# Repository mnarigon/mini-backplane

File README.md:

## A 4-slot S-100 bus mini-backplane with power supply chassis.

#### Description

This is a 4-slot S-100 bus mini-backplane with power supply chassis.

It is intended for someone interested in building and running S-100 bus cards, possibly as a first project or for use on a test bench.

Features:
- 4 slots.
- Chassis is designed for three Mean Well switching power supplies to provide 8V, 16V, and -16V in one unit. The maximum 8V current is 10 amps.
- Jumpers to ground for S-100 pins 20, 53, and 70. Some pre-IEEE-696 cards use these pins for signals where IEEE-696 defines these pins as grounds.
- Connector for a reset switch.

#### Mini-backplane Design Files

The mini-backplane design files in KiCad 7 are in the kicad directory.

The generated mini-backplane Gerber and drill files are in the file mini-backplane-gerbers.zip.

#### Chassis Design Files

The bill of materials is in the bom directory.

There is a poorly-executed layout drawing for the chassis holes in the chassis directory.

At maximum output power the power supplies will dissipate ~10W. A simple thermal
analysis indicated that cooling would be OK without any holes in the chassis.
However, I have a friend with a CNC mill who was willing mill the chassis, so I
added the cooling slots as shown on the drawing.

#### Chassis Assembly Notes

The chassis is tight, if I built this again I would select a slightly larger chassis. The height is OK, but a chassis that was an inch or two longer and wider would make it easier to wire and install the power supplies.

The power switch didn’t sit tight in its mounting hole. The chassis wall thickness is 0.040 inch and the switch might have been designed for a thicker walled chassis. I used some hot glue on the switch to keep it from moving.

Wait to install the IEC power connector until you have the power supplies installed. You will need clearance to install the 16V and -16V power supplies.

#### Assembly Steps

1. Make up the wires that will go to the IEC power connector quick connect terminals.
1. Make up the wires that go from the backplane connectors to the power supplies.
1. Wire the 16V and -16V power supplies to each other and the backplane cables.
1. Wire the fuse holder and power switch.
1. Epoxy two of the 4-40 by 1 inch flat-headed screws that hold the mini-backplane to the chassis. They will be hidden by the installed power supplies.
1. Mount the 8V supply and wire to the switch and IEC connector wires.
1. Mount the 16V and -16V supplies. They will fit in but it will take some persuasion.
1. Install the IEC power connector. Finish installing all the wiring.
1. Complete by mounting the backplane on the chassis.

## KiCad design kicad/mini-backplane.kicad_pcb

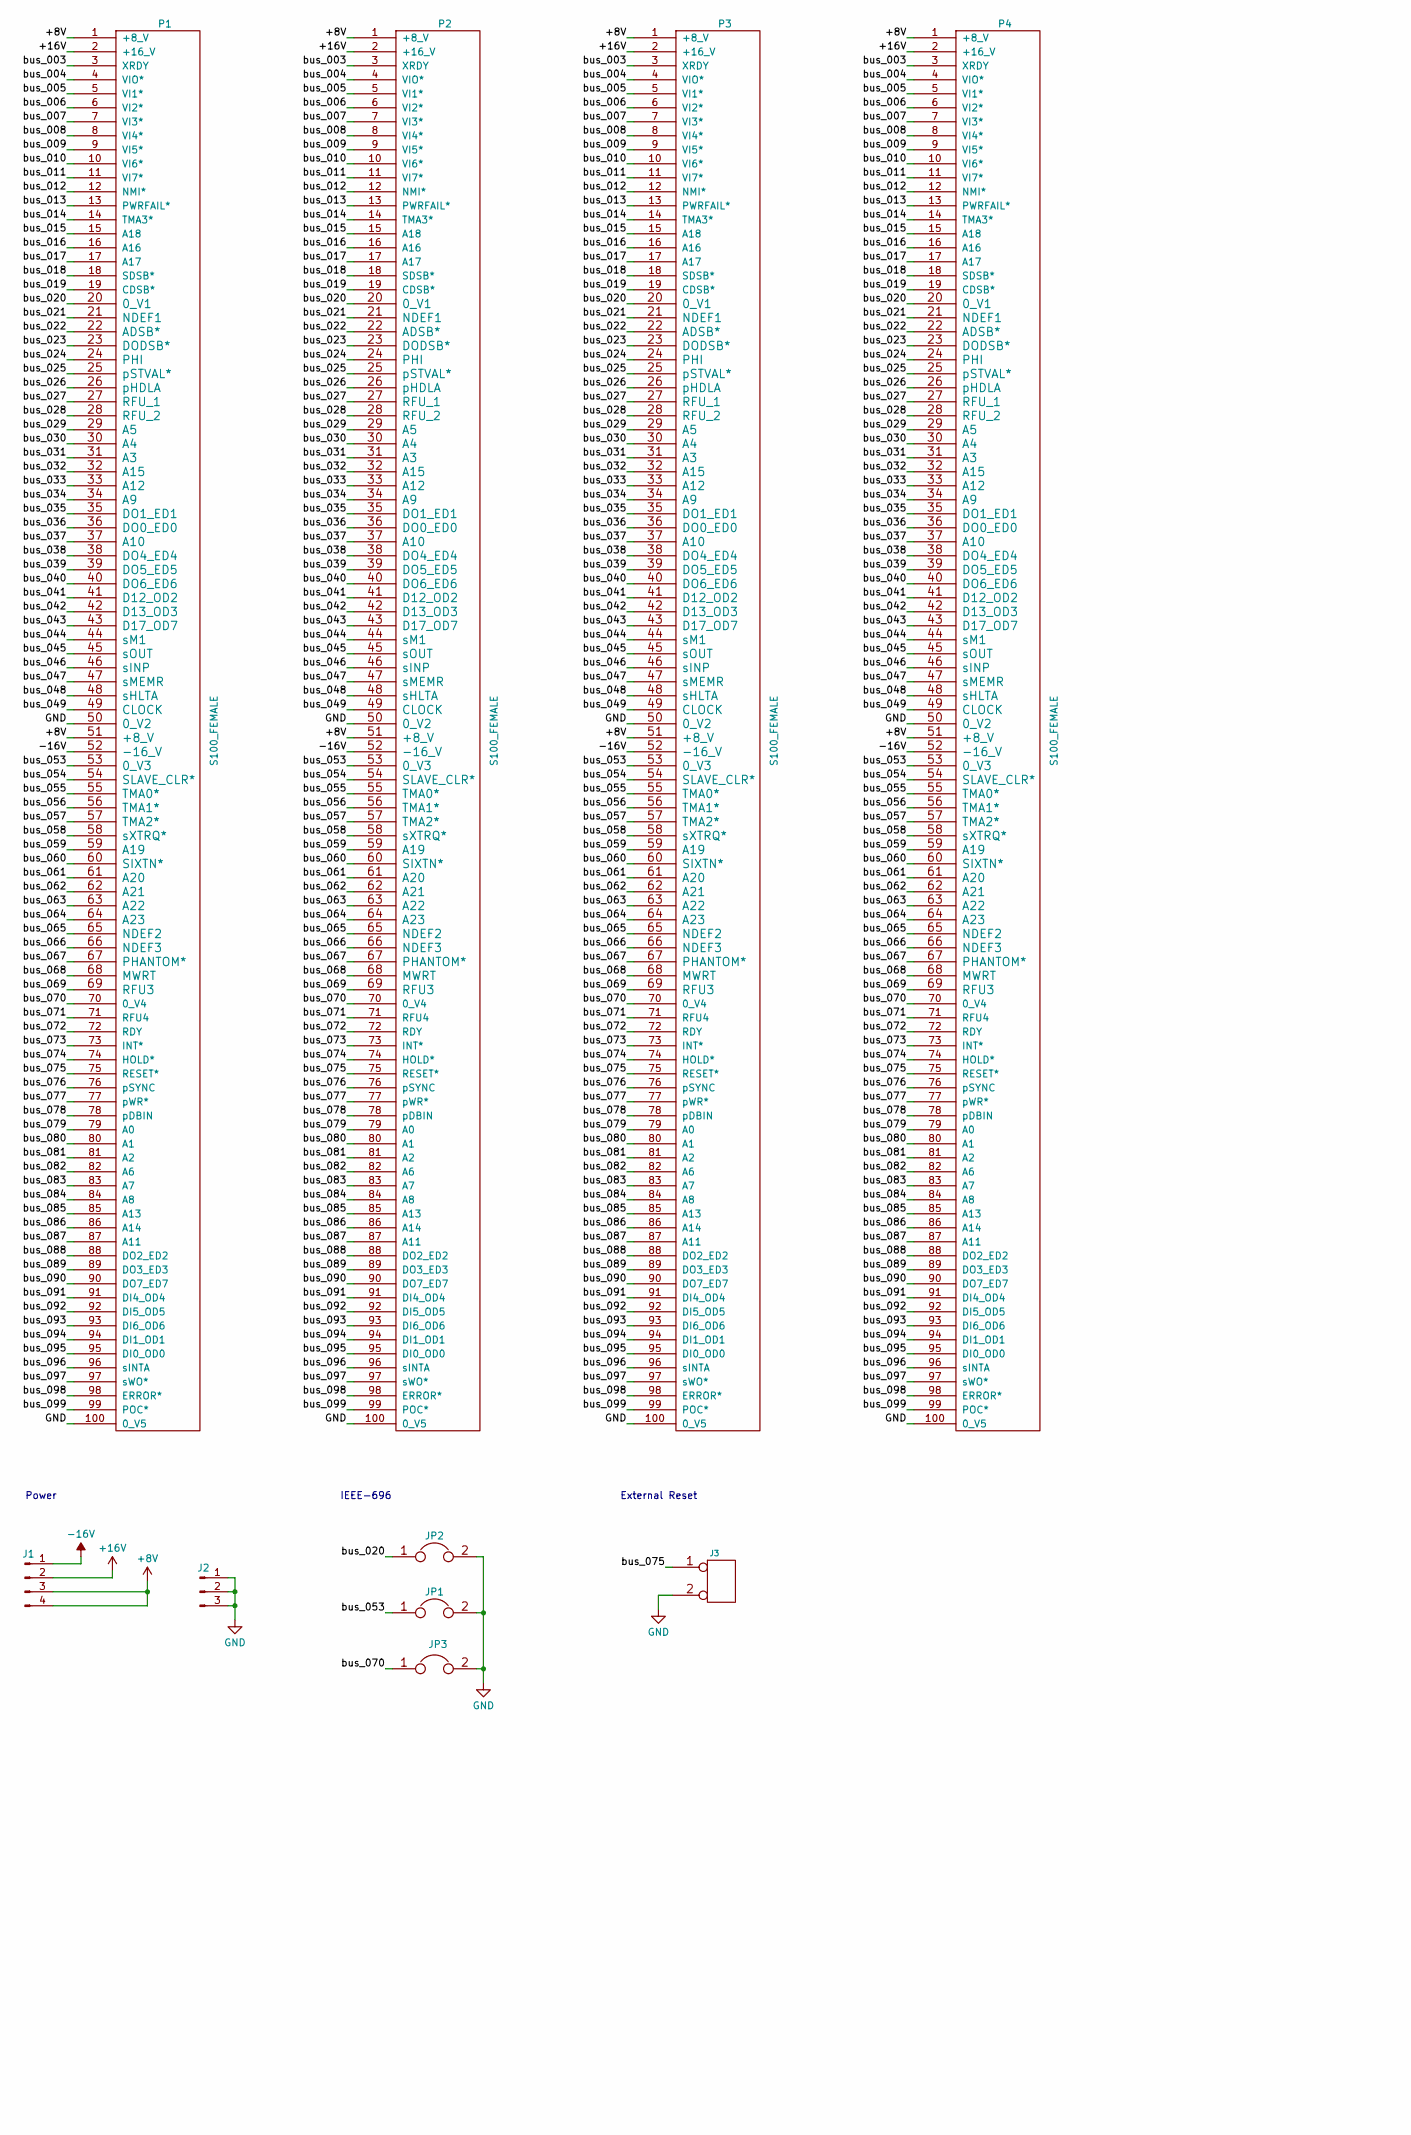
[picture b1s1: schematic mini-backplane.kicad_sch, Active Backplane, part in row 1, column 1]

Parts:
J1: Conn_01x04_Pin; AMP_640445-4
J2: Conn_01x03_Pin; AMP_640445-3
J3: Conn_01x02_Pin; AMP_640454-2
JP1, JP2, JP3: JUMPER; PinHeader_01x02_P2.54mm
P1, P2, P3, P4: S100_FEMALE; EDAC_346-100-520-202

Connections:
+8V: J1.3, J1.4, P1.1 (+8_V), P1.51 (+8_V), P2.1 (+8_V), P2.51 (+8_V), P3.1 (+8_V), P3.51 (+8_V), P4.1 (+8_V), P4.51 (+8_V)
+16V: J1.2, P1.2 (+16_V), P2.2 (+16_V), P3.2 (+16_V), P4.2 (+16_V)
-16V: J1.1, P1.52 (-16_V), P2.52 (-16_V), P3.52 (-16_V), P4.52 (-16_V)
/bus_003: P1.3 (XRDY), P2.3 (XRDY), P3.3 (XRDY), P4.3 (XRDY)
/bus_004: P1.4 (VIO*), P2.4 (VIO*), P3.4 (VIO*), P4.4 (VIO*)
/bus_005: P1.5 (VI1*), P2.5 (VI1*), P3.5 (VI1*), P4.5 (VI1*)
/bus_006: P1.6 (VI2*), P2.6 (VI2*), P3.6 (VI2*), P4.6 (VI2*)
/bus_007: P1.7 (VI3*), P2.7 (VI3*), P3.7 (VI3*), P4.7 (VI3*)
/bus_008: P1.8 (VI4*), P2.8 (VI4*), P3.8 (VI4*), P4.8 (VI4*)
/bus_009: P1.9 (VI5*), P2.9 (VI5*), P3.9 (VI5*), P4.9 (VI5*)
/bus_010: P1.10 (VI6*), P2.10 (VI6*), P3.10 (VI6*), P4.10 (VI6*)
/bus_011: P1.11 (VI7*), P2.11 (VI7*), P3.11 (VI7*), P4.11 (VI7*)
/bus_012: P1.12 (NMI*), P2.12 (NMI*), P3.12 (NMI*), P4.12 (NMI*)
/bus_013: P1.13 (PWRFAIL*), P2.13 (PWRFAIL*), P3.13 (PWRFAIL*), P4.13 (PWRFAIL*)
/bus_014: P1.14 (TMA3*), P2.14 (TMA3*), P3.14 (TMA3*), P4.14 (TMA3*)
/bus_015: P1.15 (A18), P2.15 (A18), P3.15 (A18), P4.15 (A18)
/bus_016: P1.16 (A16), P2.16 (A16), P3.16 (A16), P4.16 (A16)
/bus_017: P1.17 (A17), P2.17 (A17), P3.17 (A17), P4.17 (A17)
/bus_018: P1.18 (SDSB*), P2.18 (SDSB*), P3.18 (SDSB*), P4.18 (SDSB*)
/bus_019: P1.19 (CDSB*), P2.19 (CDSB*), P3.19 (CDSB*), P4.19 (CDSB*)
/bus_020: JP2.1, P1.20 (0_V1), P2.20 (0_V1), P3.20 (0_V1), P4.20 (0_V1)
/bus_021: P1.21 (NDEF1), P2.21 (NDEF1), P3.21 (NDEF1), P4.21 (NDEF1)
/bus_022: P1.22 (ADSB*), P2.22 (ADSB*), P3.22 (ADSB*), P4.22 (ADSB*)
/bus_023: P1.23 (DODSB*), P2.23 (DODSB*), P3.23 (DODSB*), P4.23 (DODSB*)
/bus_024: P1.24 (PHI), P2.24 (PHI), P3.24 (PHI), P4.24 (PHI)
/bus_025: P1.25 (pSTVAL*), P2.25 (pSTVAL*), P3.25 (pSTVAL*), P4.25 (pSTVAL*)
/bus_026: P1.26 (pHDLA), P2.26 (pHDLA), P3.26 (pHDLA), P4.26 (pHDLA)
/bus_027: P1.27 (RFU_1), P2.27 (RFU_1), P3.27 (RFU_1), P4.27 (RFU_1)
/bus_028: P1.28 (RFU_2), P2.28 (RFU_2), P3.28 (RFU_2), P4.28 (RFU_2)
/bus_029: P1.29 (A5), P2.29 (A5), P3.29 (A5), P4.29 (A5)
/bus_030: P1.30 (A4), P2.30 (A4), P3.30 (A4), P4.30 (A4)
/bus_031: P1.31 (A3), P2.31 (A3), P3.31 (A3), P4.31 (A3)
/bus_032: P1.32 (A15), P2.32 (A15), P3.32 (A15), P4.32 (A15)
/bus_033: P1.33 (A12), P2.33 (A12), P3.33 (A12), P4.33 (A12)
/bus_034: P1.34 (A9), P2.34 (A9), P3.34 (A9), P4.34 (A9)
/bus_035: P1.35 (DO1_ED1), P2.35 (DO1_ED1), P3.35 (DO1_ED1), P4.35 (DO1_ED1)
/bus_036: P1.36 (DO0_ED0), P2.36 (DO0_ED0), P3.36 (DO0_ED0), P4.36 (DO0_ED0)
/bus_037: P1.37 (A10), P2.37 (A10), P3.37 (A10), P4.37 (A10)
/bus_038: P1.38 (DO4_ED4), P2.38 (DO4_ED4), P3.38 (DO4_ED4), P4.38 (DO4_ED4)
/bus_039: P1.39 (DO5_ED5), P2.39 (DO5_ED5), P3.39 (DO5_ED5), P4.39 (DO5_ED5)
/bus_040: P1.40 (DO6_ED6), P2.40 (DO6_ED6), P3.40 (DO6_ED6), P4.40 (DO6_ED6)
/bus_041: P1.41 (D12_OD2), P2.41 (D12_OD2), P3.41 (D12_OD2), P4.41 (D12_OD2)
/bus_042: P1.42 (D13_OD3), P2.42 (D13_OD3), P3.42 (D13_OD3), P4.42 (D13_OD3)
/bus_043: P1.43 (D17_OD7), P2.43 (D17_OD7), P3.43 (D17_OD7), P4.43 (D17_OD7)
/bus_044: P1.44 (sM1), P2.44 (sM1), P3.44 (sM1), P4.44 (sM1)
/bus_045: P1.45 (sOUT), P2.45 (sOUT), P3.45 (sOUT), P4.45 (sOUT)
/bus_046: P1.46 (sINP), P2.46 (sINP), P3.46 (sINP), P4.46 (sINP)
/bus_047: P1.47 (sMEMR), P2.47 (sMEMR), P3.47 (sMEMR), P4.47 (sMEMR)
/bus_048: P1.48 (sHLTA), P2.48 (sHLTA), P3.48 (sHLTA), P4.48 (sHLTA)
/bus_049: P1.49 (CLOCK), P2.49 (CLOCK), P3.49 (CLOCK), P4.49 (CLOCK)
/bus_053: JP1.1, P1.53 (0_V3), P2.53 (0_V3), P3.53 (0_V3), P4.53 (0_V3)
/bus_054: P1.54 (SLAVE_CLR*), P2.54 (SLAVE_CLR*), P3.54 (SLAVE_CLR*), P4.54 (SLAVE_CLR*)
/bus_055: P1.55 (TMA0*), P2.55 (TMA0*), P3.55 (TMA0*), P4.55 (TMA0*)
/bus_056: P1.56 (TMA1*), P2.56 (TMA1*), P3.56 (TMA1*), P4.56 (TMA1*)
/bus_057: P1.57 (TMA2*), P2.57 (TMA2*), P3.57 (TMA2*), P4.57 (TMA2*)
/bus_058: P1.58 (sXTRQ*), P2.58 (sXTRQ*), P3.58 (sXTRQ*), P4.58 (sXTRQ*)
/bus_059: P1.59 (A19), P2.59 (A19), P3.59 (A19), P4.59 (A19)
/bus_060: P1.60 (SIXTN*), P2.60 (SIXTN*), P3.60 (SIXTN*), P4.60 (SIXTN*)
/bus_061: P1.61 (A20), P2.61 (A20), P3.61 (A20), P4.61 (A20)
/bus_062: P1.62 (A21), P2.62 (A21), P3.62 (A21), P4.62 (A21)
/bus_063: P1.63 (A22), P2.63 (A22), P3.63 (A22), P4.63 (A22)
/bus_064: P1.64 (A23), P2.64 (A23), P3.64 (A23), P4.64 (A23)
/bus_065: P1.65 (NDEF2), P2.65 (NDEF2), P3.65 (NDEF2), P4.65 (NDEF2)
/bus_066: P1.66 (NDEF3), P2.66 (NDEF3), P3.66 (NDEF3), P4.66 (NDEF3)
/bus_067: P1.67 (PHANTOM*), P2.67 (PHANTOM*), P3.67 (PHANTOM*), P4.67 (PHANTOM*)
/bus_068: P1.68 (MWRT), P2.68 (MWRT), P3.68 (MWRT), P4.68 (MWRT)
/bus_069: P1.69 (RFU3), P2.69 (RFU3), P3.69 (RFU3), P4.69 (RFU3)
/bus_070: JP3.1, P1.70 (0_V4), P2.70 (0_V4), P3.70 (0_V4), P4.70 (0_V4)
/bus_071: P1.71 (RFU4), P2.71 (RFU4), P3.71 (RFU4), P4.71 (RFU4)
/bus_072: P1.72 (RDY), P2.72 (RDY), P3.72 (RDY), P4.72 (RDY)
/bus_073: P1.73 (INT*), P2.73 (INT*), P3.73 (INT*), P4.73 (INT*)
/bus_074: P1.74 (HOLD*), P2.74 (HOLD*), P3.74 (HOLD*), P4.74 (HOLD*)
/bus_075: J3.1, P1.75 (RESET*), P2.75 (RESET*), P3.75 (RESET*), P4.75 (RESET*)
/bus_076: P1.76 (pSYNC), P2.76 (pSYNC), P3.76 (pSYNC), P4.76 (pSYNC)
/bus_077: P1.77 (pWR*), P2.77 (pWR*), P3.77 (pWR*), P4.77 (pWR*)
/bus_078: P1.78 (pDBIN), P2.78 (pDBIN), P3.78 (pDBIN), P4.78 (pDBIN)
/bus_079: P1.79 (A0), P2.79 (A0), P3.79 (A0), P4.79 (A0)
/bus_080: P1.80 (A1), P2.80 (A1), P3.80 (A1), P4.80 (A1)
/bus_081: P1.81 (A2), P2.81 (A2), P3.81 (A2), P4.81 (A2)
/bus_082: P1.82 (A6), P2.82 (A6), P3.82 (A6), P4.82 (A6)
/bus_083: P1.83 (A7), P2.83 (A7), P3.83 (A7), P4.83 (A7)
/bus_084: P1.84 (A8), P2.84 (A8), P3.84 (A8), P4.84 (A8)
/bus_085: P1.85 (A13), P2.85 (A13), P3.85 (A13), P4.85 (A13)
/bus_086: P1.86 (A14), P2.86 (A14), P3.86 (A14), P4.86 (A14)
/bus_087: P1.87 (A11), P2.87 (A11), P3.87 (A11), P4.87 (A11)
/bus_088: P1.88 (DO2_ED2), P2.88 (DO2_ED2), P3.88 (DO2_ED2), P4.88 (DO2_ED2)
/bus_089: P1.89 (DO3_ED3), P2.89 (DO3_ED3), P3.89 (DO3_ED3), P4.89 (DO3_ED3)
/bus_090: P1.90 (DO7_ED7), P2.90 (DO7_ED7), P3.90 (DO7_ED7), P4.90 (DO7_ED7)
/bus_091: P1.91 (DI4_OD4), P2.91 (DI4_OD4), P3.91 (DI4_OD4), P4.91 (DI4_OD4)
/bus_092: P1.92 (DI5_OD5), P2.92 (DI5_OD5), P3.92 (DI5_OD5), P4.92 (DI5_OD5)
/bus_093: P1.93 (DI6_OD6), P2.93 (DI6_OD6), P3.93 (DI6_OD6), P4.93 (DI6_OD6)
/bus_094: P1.94 (DI1_OD1), P2.94 (DI1_OD1), P3.94 (DI1_OD1), P4.94 (DI1_OD1)
/bus_095: P1.95 (DI0_OD0), P2.95 (DI0_OD0), P3.95 (DI0_OD0), P4.95 (DI0_OD0)
/bus_096: P1.96 (sINTA), P2.96 (sINTA), P3.96 (sINTA), P4.96 (sINTA)
/bus_097: P1.97 (sWO*), P2.97 (sWO*), P3.97 (sWO*), P4.97 (sWO*)
/bus_098: P1.98 (ERROR*), P2.98 (ERROR*), P3.98 (ERROR*), P4.98 (ERROR*)
/bus_099: P1.99 (POC*), P2.99 (POC*), P3.99 (POC*), P4.99 (POC*)
GND: J2.1, J2.2, J2.3, J3.2 (PM), JP1.2, JP2.2, JP3.2, P1.50 (0_V2), P1.100 (0_V5), P2.50 (0_V2), P2.100 (0_V5), P3.50 (0_V2), P3.100 (0_V5), P4.50 (0_V2), P4.100 (0_V5)

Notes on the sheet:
Power
4-slot S-100 Bus Mini-Backplane
External Reset
IEEE-696

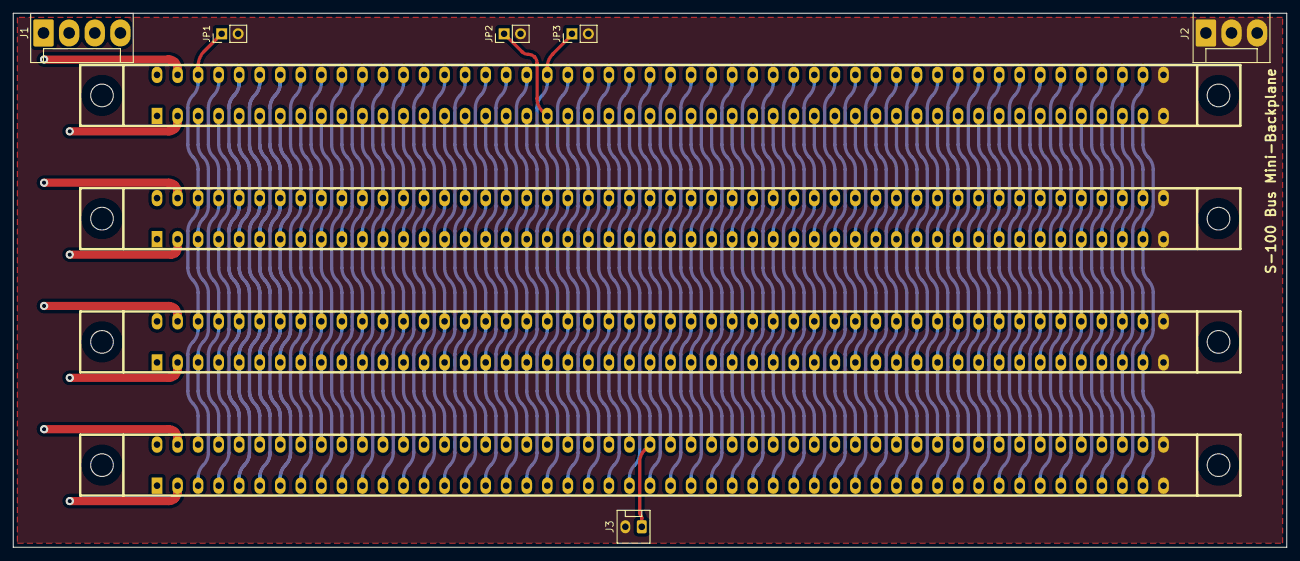
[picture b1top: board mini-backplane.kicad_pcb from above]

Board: 2 copper layers, 196.8 x 82.6 mm, 10 parts (0 on the bottom side), 98 nets.

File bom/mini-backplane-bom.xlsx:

Mini-Backplane BOM
Designator | Part | Value | Footprint | Manufacturer | Quantity | Digikey Part Number | Unit Price | Total
J1 | Header, Male Pins |  | AMP_640445-4 |  | 1 | A1972-ND | 0.27 | 0.27
J2 | Header, Male Pins |  | AMP_640445-3 |  | 1 | A19890-ND | 0.26 | 0.26
J3 | Header, Male Pins |  | AMP_640454-2 |  | 1 | A19423-ND | 0.15 | 0.15
JP1-JP3 | Pin Header |  | PinHeader_01x02_P2.54mm |  | 3 | 609-3507-ND | 0.16 | 0.48
 | Mating Connector for J1 |  |  |  | 1 | A24113-ND | 0.25 | 0.25
 | Mating Connector for J2 |  |  |  | 1 | A24112-ND | 0.2 | 0.2
 | Mating Connector for J3 |  |  |  | 1 | A99613-ND | 0.15 | 0.15
 | Contacts for J1, J2 |  |  |  | 7 | A31396-ND | 0.35 | 2.45
 | Contacts for J3 |  |  |  | 2 | A100453CT-ND | 0.1 | 0.2
 | Shunts for JP1-JP3 |  |  |  | 3 | S9000-ND | 0.1 | 0.3
P1-P4 | Card Edge Connector |  | EDAC_346-100-520-202 |  | 4 | EDC346102-ND or ESA50DRSH-S288-ND | 15.48 | 61.92
 | Chassis |  | 10*6*2in (L*W*H) | Hammond 1444-16 | 1 | HM264-ND | 20.48 | 20.48
 | Cover |  | 10*6in (L*W*H) | Hammond 1434-16 | 1 | HM280-ND | 11 | 11
 | 8V Power Supply |  | 159*97*30mm (L*W*H) | Mean Well RSP 75-7.5 | 1 | 1866-4289-ND | 36.93 | 36.93
 | +16V and -16V Power Supplies |  | 62.5*51*28mm (L*W*H) | Mean Well RS-15-15 | 2 | 1866-4129-ND | 10.86 | 21.72
 | Fuse Holder 10 A 250V 1 Circuit Cartridge Panel Mount |  |  | Wurth | 1 | 732-11380-ND | 1.86 | 1.86
 | Fuse 1.25A 250V 5x20mm Slo-blow |  |  | Bel Fuse | 1 | 507-1247-ND | 0.25 | 0.25
 | Rocker Switch SPST 10A (AC) 125 V Panel Mount, Snap-In |  |  | E-Switch | 1 | EG5617-ND | 0.66 | 0.66
 | Power Entry, IEC Appliance, 10A |  |  | DIT | 1 | 4761-DAC-12F-ND | 0.73 | 0.73
 | Grommet, 0.375in, Rubber, Black |  |  | Keystone Electronics | 1 | 36-745-ND | 0.27 | 0.27
 | Spade Connector, 18-22AWG, M3 (for +8V PS) |  |  |  | 10 | A135212-ND | 0.45 | 4.5
 | Spade Connector, 18-22AWG, M3 (for +/-16V PS) |  |  |  | 14 | 298-20471-1-ND | 0.419 | 5.866
 | Quick-Connect Connector, 4.7mm |  |  |  | 5 | A27806CT-ND | 0.26 | 1.3
 | Bumper Cylindrical, Recessed Center 0.500" Dia |  |  | Keystone Electronics | 4 | 36-720-ND | 0.32 | 1.28
 | Round Spacer #4 Nylon, 3/8in |  |  | Bivar, Inc. | 4 | 492-1091-ND | 0.1 | 0.4
 | 6-32xL3/8 in Self-Tapping Sheet Metal Screws (for cover) |  |  | Bolt Depot | 4
 | 4-40xL1/2 in Pan Head Machine Screw (for bumper feet) |  |  | Bolt Depot | 4
 | #4 washer (for bumper feet) |  |  | Bolt Depot | 4
 | 4-40 nut (for bumper feet, double to lock) |  |  | Bolt Depot | 8
 | 4-40xL1 in Flat Head Machine Screw (for standoffs) |  |  | Bolt Depot | 4
 | 4-40 K-nut (for standoffs) |  |  | Bolt Depot | 4
 | M3xL5 Hardware (for PS mount) |  |  | Bolt Depot | 6
 | M3 washer (for PS mount) |  |  | Bolt Depot | 6
 | M3 lock washer (for PS mount) |  |  | Bolt Depot | 6
 | Black/White/Green/Red/Brown/Blue/Orange/Yellow 18-Gauge Wire
Total |  |  |  |  |  |  |  | 173.876

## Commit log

2023-12-26 Initial import
2023-12-26 reorganize repository
